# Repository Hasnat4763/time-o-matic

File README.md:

# time-o-matic

This is a pc statistics displayer which uses USB to transmit RTSS data over serial.

I made this because during gameplay it is pretty disorienting while MSI afterburner is giving an overlay and I dont have any display on my casing to do the same work.

# PCB

# CAD

# Schematic

# Bill of Materials (BOM)

## Component List

| Designator | Footprint | Qty | Value | Price | Supplier Link |
|------------|-----------|-----|-------|-------|---------------|
| C1, C7, C8 | 0603 | 3 | 10uF | $3.30 | [AliExpress](https://www.aliexpress.com/item/1005007464553853.html) |
| C2 | 0603 | 1 | 100nF | $1.20 | [AliExpress](https://www.aliexpress.com/item/1005008841132875.html) |
| C3 | 0603 | 1 | 22uF | $1.20 | [AliExpress](https://www.aliexpress.com/item/1005008841132875.html) |
| C4 | 0603 | 1 | 220pF | $1.20 | [AliExpress](https://www.aliexpress.com/item/1005008841132875.html) |
| D1 | D_SOD-882 | 1 | D_Schottky | $0.84 | [AliExpress](https://www.aliexpress.com/item/1005008567183952.html) |
| J2 | USB_C_Receptacle_GCT_USB4085 | 1 | USB_C_Receptacle_USB2.0_14P | $8.85 | [AliExpress](https://www.aliexpress.com/item/1005007627491218.html) |
| L1 | 0603 | 1 | 10uH | $1.30 | [AliExpress](https://www.aliexpress.com/item/1005004900337516.html) |
| R1 | 0603 | 1 | 100k | $0.66 | [AliExpress](https://www.aliexpress.com/item/1005001793547200.html) |
| R10, R9 | 0603 | 2 | 5.1k | $0.90 | [AliExpress](https://www.aliexpress.com/item/1005006468967431.html) |
| R11, R12 | 0603 | 2 | 10k | $0.62 | [AliExpress](https://www.aliexpress.com/item/1005001793547200.html) |
| R2 | 0603 | 1 | 24.9k | $0.87 | [AliExpress](https://www.aliexpress.com/item/1005006468967431.html) |
| R3 | 0603 | 1 | 200k | $0.62 | [AliExpress](https://www.aliexpress.com/item/1005001793547200.html) |
| R4 | 0603 | 1 | 40.2k | $0.87 | [AliExpress](https://www.aliexpress.com/item/1005006468967431.html) |
| R5 | 0603 | 1 | 124k | $0.87 | [AliExpress](https://www.aliexpress.com/item/1005006468967431.html) |
| R6 | 0603 | 1 | 68.1k | $0.82 | [AliExpress](https://www.aliexpress.com/item/1005005478816023.html) |
| U1 | ESP32-WROOM-32E | 1 | ESP32-WROOM-E | $3.30 | [AliExpress](https://www.aliexpress.com/item/1005005859646446.html) |
| U2 | SOIC8E_MPS_MNP-L | 1 | MP1584EN-LF-P | $2.80 | [AliExpress](https://www.aliexpress.com/item/32859231863.html) |
| U4 | SOIC-16_3.9x9.9mm_P1.27mm | 1 | CH340C | $3.30 | [AliExpress](https://www.aliexpress.com/item/1005005771405592.html) |
|    |                           |   | PCB and Stencil| $22 | [JLCPCB](https://hc-cdn.hel1.your-objectstorage.com/s/v3/1d6a6af164f7687632a73b3bdf67f14b9d156949_image.png) |
|    |                           |  | Case | Printing Legion |

## Cost Summary

**Total Cost: $32.72**

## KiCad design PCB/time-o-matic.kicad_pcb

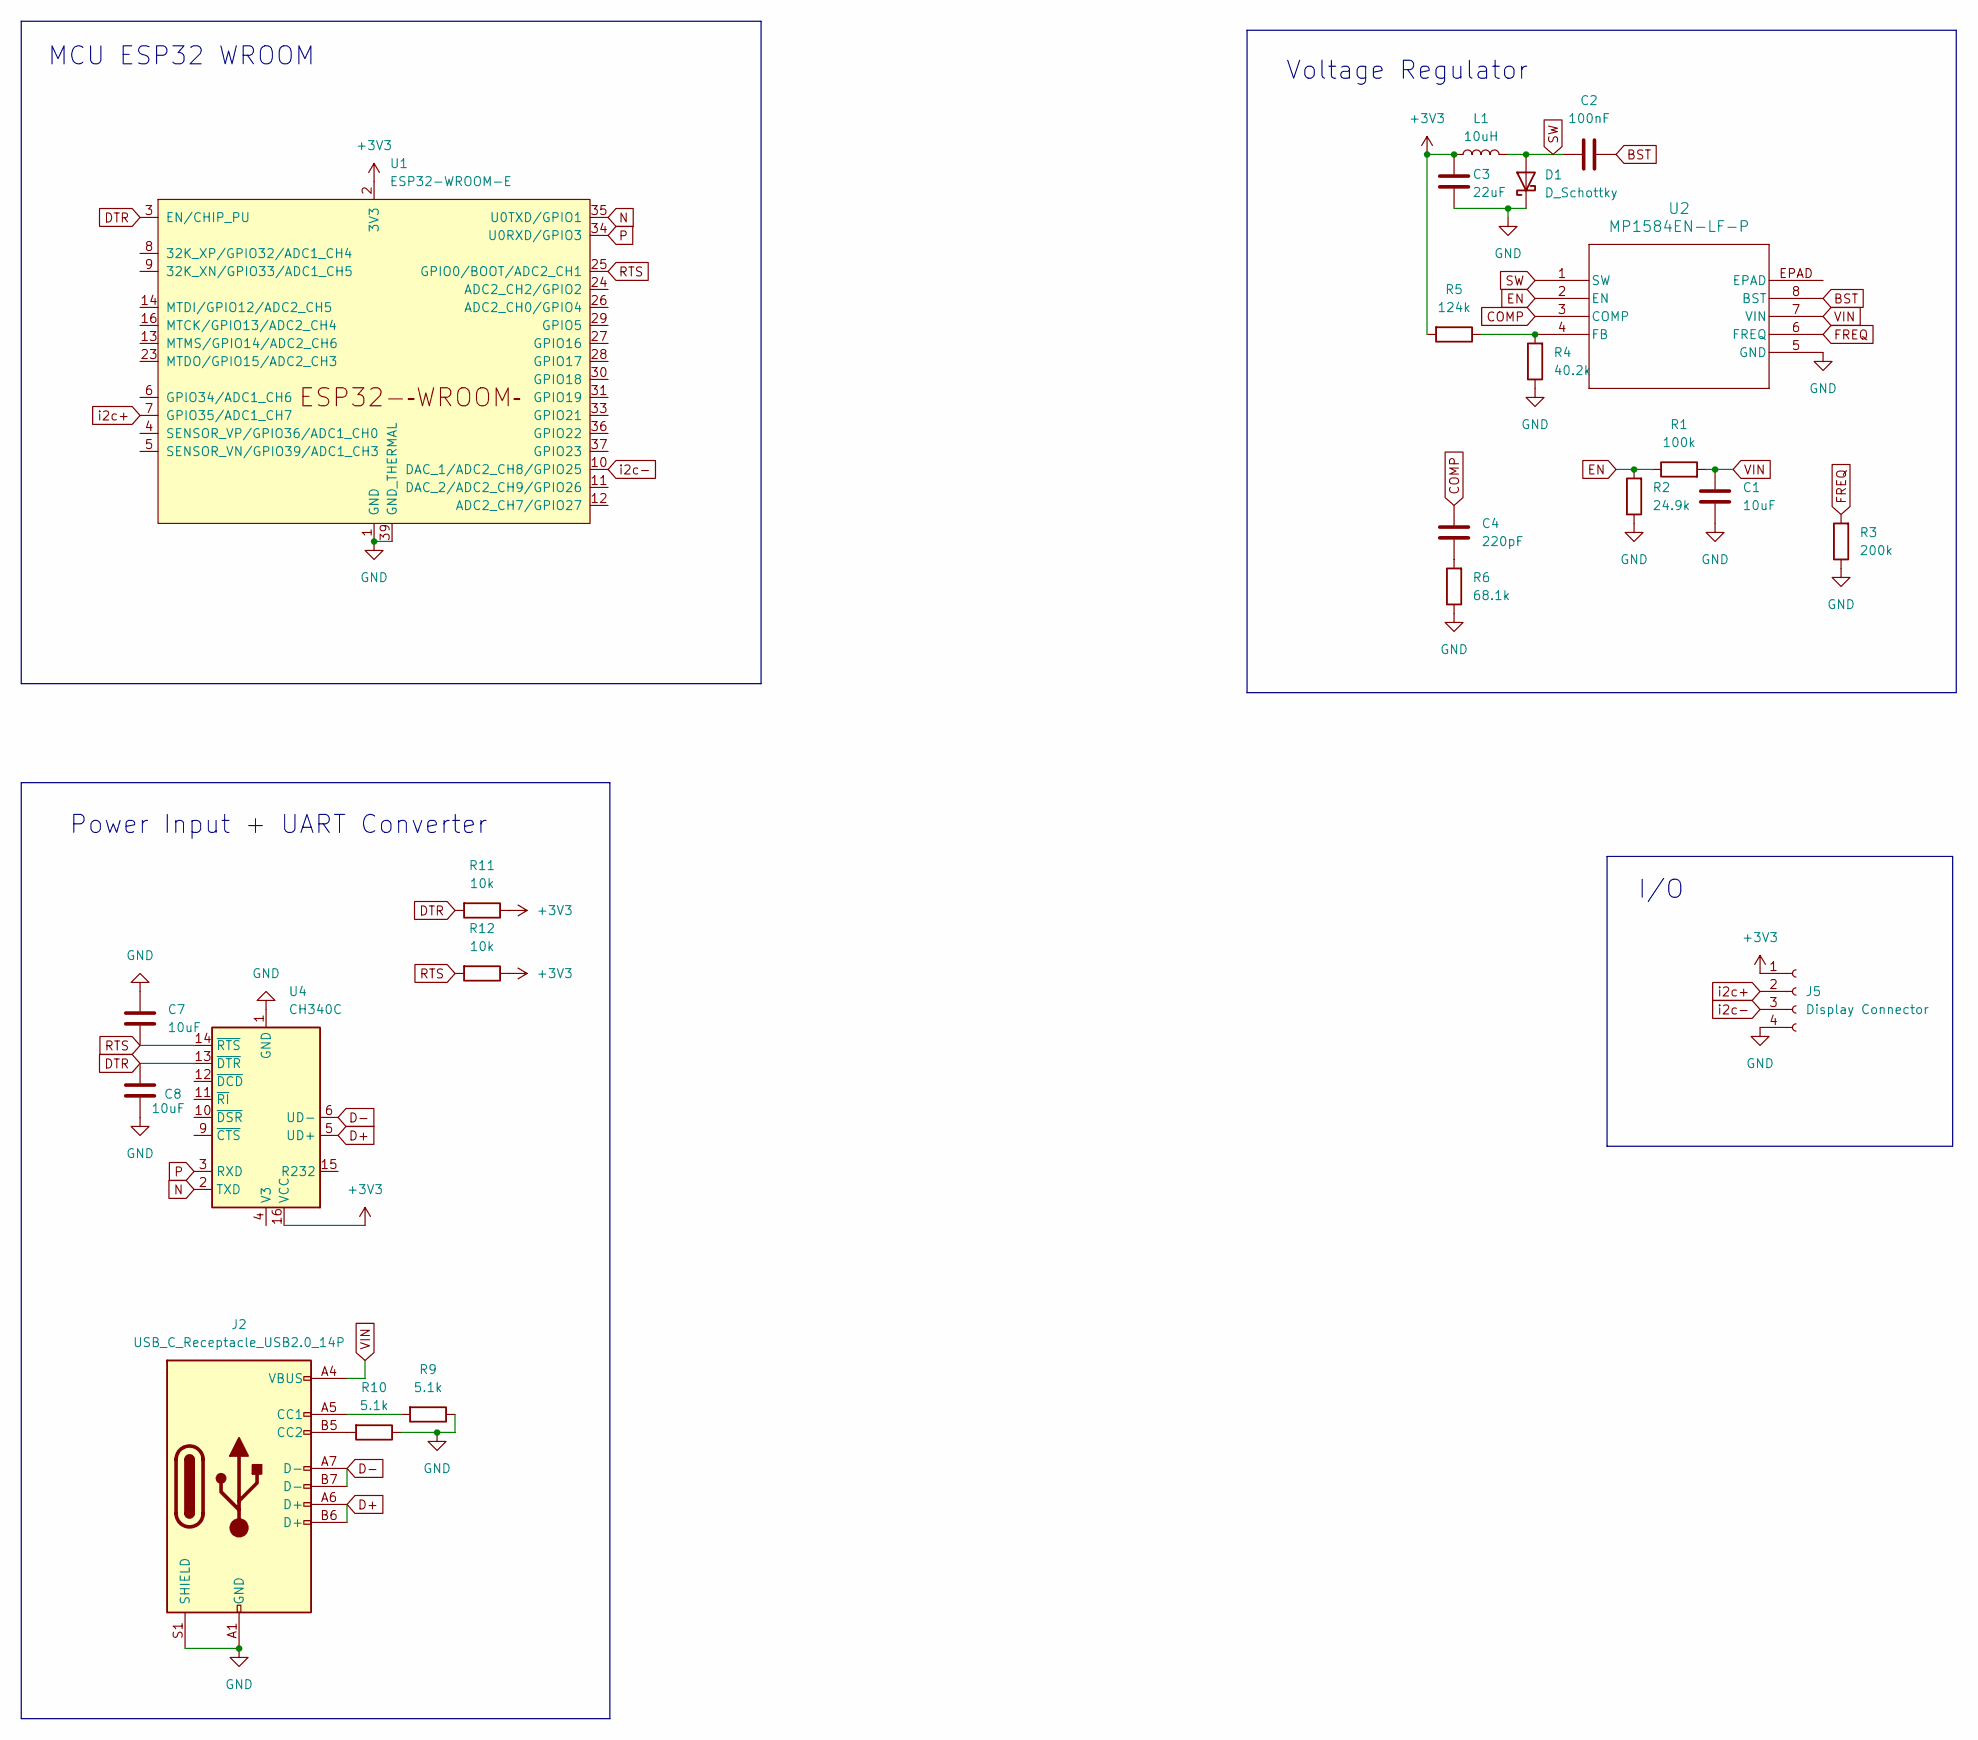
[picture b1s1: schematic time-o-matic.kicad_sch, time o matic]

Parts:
C1, C7, C8: 10uF; C_0603_1608Metric_Pad1.08x0.95mm_HandSolder
C2: 100nF; C_0603_1608Metric_Pad1.08x0.95mm_HandSolder
C3: 22uF; C_0603_1608Metric_Pad1.08x0.95mm_HandSolder
C4: 220pF; C_0603_1608Metric_Pad1.08x0.95mm_HandSolder
D1: D_Schottky; D_SOD-882
J2: USB_C_Receptacle_USB2.0_14P; USB_C_Receptacle_GCT_USB4085
J5: Display Connector; PinHeader_1x04_P2.54mm_Vertical
L1: 10uH; L_0603_1608Metric_Pad1.05x0.95mm_HandSolder
R1: 100k; R_0603_1608Metric_Pad0.98x0.95mm_HandSolder
R2: 24.9k; R_0603_1608Metric_Pad0.98x0.95mm_HandSolder
R3: 200k; R_0603_1608Metric_Pad0.98x0.95mm_HandSolder
R4: 40.2k; R_0603_1608Metric_Pad0.98x0.95mm_HandSolder
R5: 124k; R_0603_1608Metric_Pad0.98x0.95mm_HandSolder
R6: 68.1k; R_0603_1608Metric_Pad0.98x0.95mm_HandSolder
R9, R10: 5.1k; R_0603_1608Metric_Pad0.98x0.95mm_HandSolder
R11, R12: 10k; R_0603_1608Metric_Pad0.98x0.95mm_HandSolder
U1: ESP32-WROOM-E; ESP32-WROOM-32E
U2: MP1584EN-LF-P; SOIC8E_MPS_MNP-L
U4: CH340C; SOIC-16_3.9x9.9mm_P1.27mm

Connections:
+3V3: C3.1, J5.1, L1.1, R5.2, R11.1, R12.1, U1.2 (3V3), U4.16 (VCC)
BST: C2.1, U2.8 (BST)
COMP: C4.1, U2.3 (COMP)
D+: J2.A6 (D+), J2.B6 (D+), U4.5 (UD+)
D-: J2.A7 (D-), J2.B7 (D-), U4.6 (UD-)
DTR: C8.2, R11.2, U1.3 (EN/CHIP_PU), U4.13 (~DTR)
EN: R1.1, R2.2, U2.2 (EN)
FREQ: R3.2, U2.6 (FREQ)
GND: C1.2, C3.2, C7.2, C8.1, D1.1 (K), J2.A1 (GND), J2.A12 (GND), J2.B1 (GND), J2.B12 (GND), J2.S1 (SHIELD), J5.4, R2.1, R3.1, R4.1, R6.1, R9.1, R10.1, U1.1 (GND), U1.15 (GND), U1.38 (GND), U1.39 (GND_THERMAL), U2.5 (GND), U4.1 (GND)
N: U1.35 (U0TXD/GPIO1), U4.2 (TXD)
unnamed: C4.2, R6.2
unnamed: J2.A5 (CC1), R9.2
unnamed: J2.B5 (CC2), R10.2
unnamed: R4.2, R5.1, U2.4 (FB)
P: U1.34 (U0RXD/GPIO3), U4.3 (RXD)
RTS: C7.1, R12.2, U1.25 (GPIO0/BOOT/ADC2_CH1), U4.14 (~RTS)
SW: C2.2, D1.2 (A), L1.2, U2.1 (SW)
VIN: C1.1, J2.A4 (VBUS), J2.A9 (VBUS), J2.B4 (VBUS), J2.B9 (VBUS), R1.2, U2.7 (VIN)
i2c+: J5.2, U1.7 (GPIO35/ADC1_CH7)
i2c-: J5.3, U1.10 (DAC_1/ADC2_CH8/GPIO25)

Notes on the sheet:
Power Input + UART Converter
Voltage Regulator
MCU ESP32 WROOM
I/O

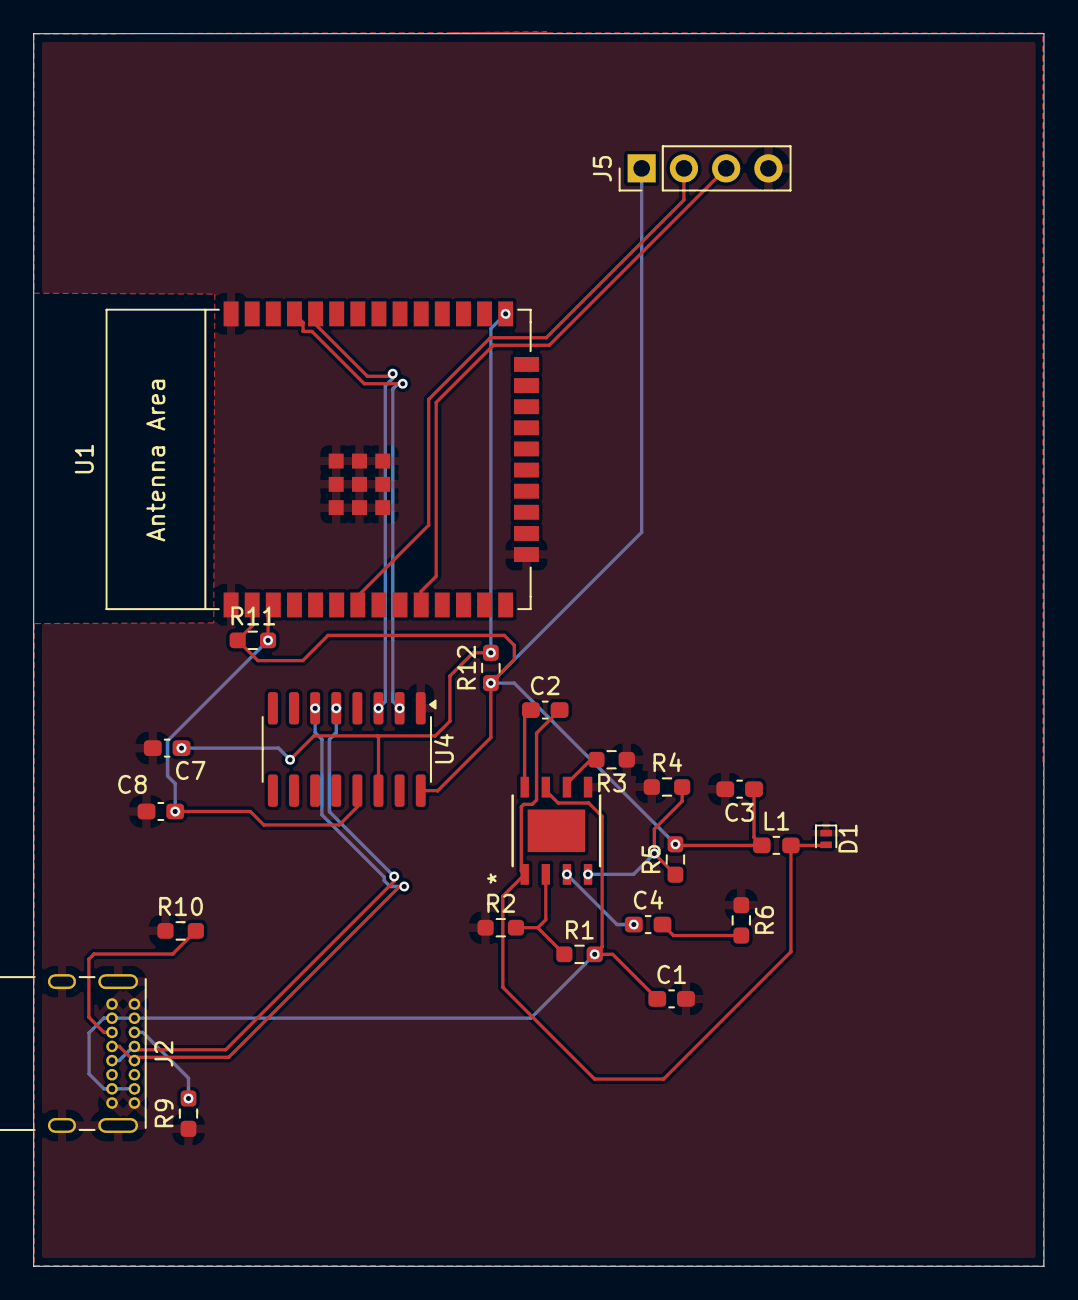
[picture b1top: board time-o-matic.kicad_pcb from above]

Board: 2 copper layers, 60.8 x 74.1 mm, 23 parts (0 on the bottom side), 20 nets.

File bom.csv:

Designator,Footprint,Quantity,Value,Price, Link
"C1, C7, C8",0603,3,10uF, $3.30, https://www.aliexpress.com/item/1005007464553853.html?spm=a2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
C2,0603,1,100nF, $1.20 ,https://www.aliexpress.com/item/1005008841132875.html?spm=a2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
C3,0603,1,22uF, $1.20 ,https://www.aliexpress.com/item/1005008841132875.html?spm=a2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
C4,0603,1,220pF, $1.20,https://www.aliexpress.com/item/1005008841132875.html?spm=a2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
D1,D_SOD-882,1,D_Schottky, $0.84,https://www.aliexpress.com/item/1005008567183952.html?spm=a2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
J2,USB_C_Receptacle_GCT_USB4085,1,USB_C_Receptacle_USB2.0_14P, $8.85,https://www.aliexpress.com/item/1005007627491218.html?spm=a2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
L1,0603,1,10uH, $1.30,https://www.aliexpress.com/item/1005004900337516.html?spm=a2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
R1,0603,1,100k, $0.66,https://www.aliexpress.com/item/1005001793547200.html?spm=a2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
"R10, R9",0603,2,5.1k, $0.90,https://www.aliexpress.com/item/1005006468967431.html?spm=a2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
"R11, R12",0603,2,10k, $0.62,https://www.aliexpress.com/item/1005001793547200.html?spm=a2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
R2,0603,1,24.9k, $0.87,https://www.aliexpress.com/item/1005006468967431.html?spm=a2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
R3,0603,1,200k, $0.62,https://www.aliexpress.com/item/1005001793547200.html?spm=a2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
R4,0603,1,40.2k, $0.87,https://www.aliexpress.com/item/1005006468967431.html?spm=a2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
R5,0603,1,124k, $0.87,https://www.aliexpress.com/item/1005006468967431.html?spm=a2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
R6,0603,1,68.1k, $0.82,https://www.aliexpress.com/item/1005005478816023.html?spm=a2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
U1,ESP32-WROOM-32E,1,ESP32-WROOM-E, $3.30,https://www.aliexpress.com/item/1005005859646446.html?spm=a2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
U2,SOIC8E_MPS_MNP-L,1,MP1584EN-LF-P, $2.80,https://www.aliexpress.com/item/32859231863.html?spm=a2g0o.p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
U4,SOIC-16_3.9x9.9mm_P1.27mm,1,CH340C, $3.30, https://www.aliexpress.com/item/1005005771405592.html?spm=a2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
,,, PCB & Stencil, $22, https://hc-cdn.hel1.your-objectstorage.com/s/v3/1d6a6af164f7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
,,, Case, Printing Legion,
Total Cost: $54.72,,,,,

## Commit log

2025-07-08 Working on schematic
2025-07-10 Updating Schematic
2025-07-26 finishing up ig
